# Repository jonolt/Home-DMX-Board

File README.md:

# Home DMX - Hardware

is a simple arduino based DMX controller to controll led lights installed in your home to be used with DMX controllers and relais.

**Please Contact me if you wonna use the board, there may be unducumented bugs.**

The Firmware can be found in a extra git repository: [Home-DMX-Firmaware](https://github.com/jonolt/Home-DMX-Firmaware).

This Project started with [Home-DMX-Control](https://github.com/jonolt/Home-DMX-Control). Firmware and hardware are now in two repositories.

## Idea

The selection for the lighting scene in daily use should be as simple as possible. Therefore exactly two push buttons are used to move up and down in a list of lighting scenes. Since I am not a fan of idle transformers, a conventional light switch is used in my application to switch the whole system on and off. In the same way a corresponding scene could be set.

The individual scenes should be adjustable directly on the controller without additional hardware. The input of the scenes works like on lighting control desks without motor faders via potentiometer and buttons. To make the firmware easy (without programmer and co) and maintainable by everyone, an Arduino was used, because it has a USB converter and the IDE is easy to use and install.

The board has a DMX output and 4 PWM/IO Outputs as well as 2 inputs for button.

## Structure

The MAX481 (U2) is a transceiver for RS-485 and RS-422 communication based on DMX. It uses the TX and RX pins of the arduino. For a visual control of the DMX communication Leds are connected via buffer (U61).

Digital inputs and outputs a isolated via optocouplers (additional circuits are required to switch larger loads).

The display is controlled serially (SPI) via the library provided by the manufacturer.

The switches can be hardware or software or both debaunced. Theres also the option to connect them via diodes (D1-D4) to a interupt pin.

The board does not has to be fully equipt with the componets.

**External Power must be disconnected when programming the Ardino, when a DC/DC converter is used!**

### Hardware Logic (Isolated)

#### Button Input

A total of 4 buttons can be placed on the pcb. While SW2 and SW3 are hard wired SW1 and SW4 can be set up in 4 different ways to safe pins to use the hardware interupt:

1. **1 buttons 0 extra IO**: SW1 or SW2 are connected only to the Interrupt pin via Diode D1/D4 or a bridge at D1/D4. If an innterupt is triggered, and neither SW2 or SW3 pin is pulled low, SW1 or SW4 must have been pressed.
2. **2 buttons 1 extra IO**: as in one but with JP1/JP2 bridged and SW1/SW4 fully equiped.
3. **2 buttons 2 extra IO**: equip all parts and bridge JP1 and JP2. Interrupt can still be used for other things.
4. **1 buttons 1 extra IO**: as in 3. but with either SW1 or SW4

Of course the swictehs can be used withiout the interrupt by ommiting the diodes. In fact even the low pass filete can be ommited with proper software debouncing.

All Switches and the interupt line are pulled up by R1 to R4 and R9. R4, C1 ect. build low pass filter for hardware debouncing and can be ommited (with the resistors bridged).

Swicth 2 and 3 have an additional Isolated input for external switches operating on another voltage level or with different ground.

#### LCD-Display

The LCD-Display is controlled by 3 Wire SPI connected to the Hardwre SPI of the microcontroller. The MISO master input is not required for the display and is kept free in case additional SPI devices are added (for example via a shield). The Backlight is PWM dimmed (D11) via the transisor Q1.

#### Expansion Connector J1 J2

The Connector(s) has the identical pinout as the Arduino Micro. Also you could use a stackable female connector strip directly with the Arduino.

#### LEDs

In addition to a power LED (D6), there are various Status LEDs on the front side (pcb-back) showing the correct function of the PWM Outputs (D20-23) and the DMX Interface (D60, D61). The LED of the Arduino can be used as a system LED if D13 is not used otherwise.

### Hardware Interfaces (Unisoltated)

All outputs and inputs (connectors) are isolated by default to each other. Resitor Bridges bridges can be apllied (1XX, 2XX) to break those isolations, see chapter Hardware Bridging.

#### X30 - Button Input

Simple current limiting Resistor R30 and R31 for diode of the photocoupler. Needs to be selected for each application by the input voltage V_IN with the formular:

R=(V_IN-V_F)/I_F, V_F=1.2V I_F=20mA

#### X40 - PWM/Output

These autputs can be used in 2 ways. As digital output with pullups and as Low Side switch (max 50mA, V_CE=0.1-0.2V).

The voltage for the pullups can cpme from the connector, directly bridged from the input power (R140) or via the linear voltage regulator U140, R142 and R143 (kater ones bridging isolation).

The emmiters of the photocouplers can be accessed directly via J41-J43 and J40-2. Conection between those can be broken at the Jumpers JP40-JP42. This way all four outputs can be used iolsated to each other.

#### X50 - Power In

Power input conssits of two parts revers voltage protection and DCDC-Converter. The reverse voltage protection is a siple p channel circuit. For the DCDC-Converter are two footprints obove each other. One for a SIL7 package (with pins 1,2,4,6 connected) and one for a SIL8 package (with pin (1, 2, (3), 6, 7 connected) to allow for different converters to be installed.

#### X60 - DMX

DMX uses the TX/RX pins of the arduino. The MAX481 (U60) is a common RS-485 tranciver. See [www.mathertel.de/Arduino/DMXShield.aspx](http://www.mathertel.de/Arduino/DMXShield.aspx) for a detailed description.

### Hardware Bridging

Danger Zone. Only assemble these components if you know what you are doing as this will bridge isolations.

#### 1XX

Bridges between unisolated interfaces:

- **R130, R131**: VIN/GND to PWM/Ouitput
- **R140, R141**: VIN/GND to Button Input

#### 2XX

Bridges between unisolated interfaces and isolated internal circuit:

- **J250, J251**: Connect these Pads with a wire to use the buildin voltage regulator of the arduino (VIN).
- **R260-R264**: Bypass isolation of DMX interface.

## License and Copyright

Copyright (C) 2019, 2020 Johannes Nolte
 
This program is free software: you can redistribute it and/or modify
it under the terms of the GNU General Public License as published by
the Free Software Foundation, version 2.1 only.

This program is distributed in the hope that it will be useful,
but WITHOUT ANY WARRANTY; without even the implied warranty of
MERCHANTABILITY or FITNESS FOR A PARTICULAR PURPOSE.  See the
GNU General Public License for more details.

You should have received a copy of the GNU General Public License
along with this program.  If not, see <https://www.gnu.org/licenses/>.

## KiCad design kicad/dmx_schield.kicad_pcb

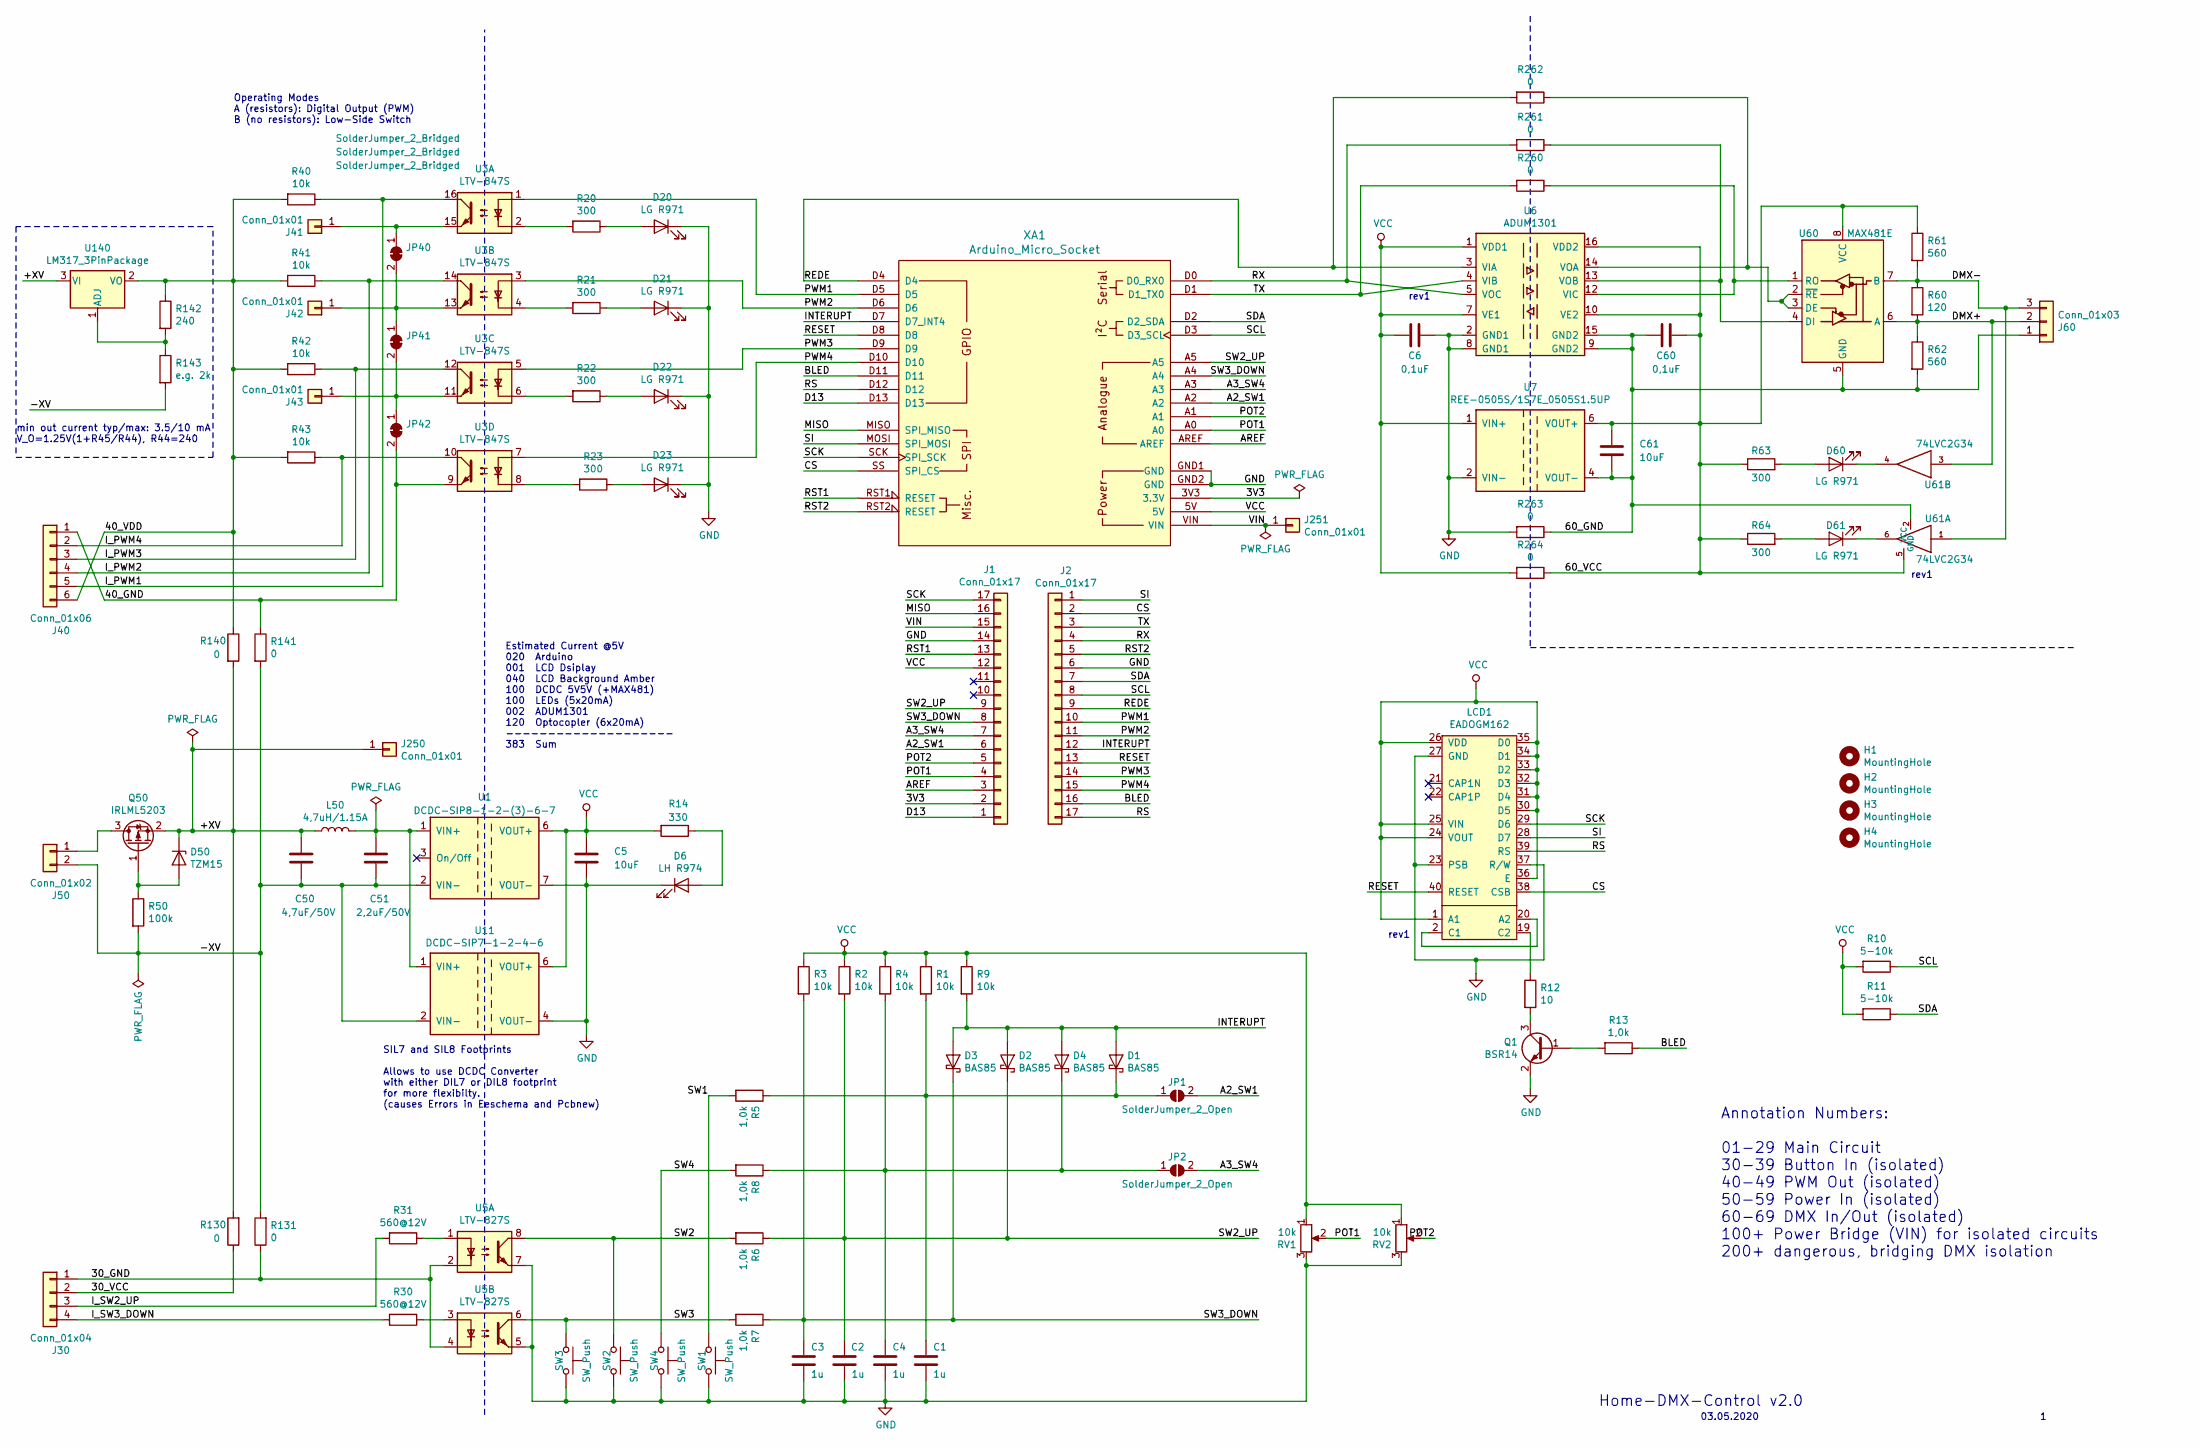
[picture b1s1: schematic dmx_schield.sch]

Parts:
C1, C2, C3, C4: 1u; C_0805_2012Metric
C5, C61: 10uF; C_1206_3216Metric
C6, C60: 0,1uF; C_0805_2012Metric
C50: 4,7uF/50V; C_1206_3216Metric
C51: 2,2uF/50V; C_1206_3216Metric
D1, D2, D3, D4: BAS85; D_MicroMELF
D6: LH R974; LED_0805_2012Metric
D20, D21, D22, D23, D60, D61: LG R971; LED_0805_2012Metric
D50: TZM15; D_SC-80
H1, H2, H3, H4: MountingHole; MountingHole_3.2mm_M3_DIN965
J1, J2: Conn_01x17; PinSocket_1x17_P2.54mm_Vertical
J30: Conn_01x04; PhoenixContact_MC_1,5_4-G-3.81_1x04_P3.81mm_Horizontal
J40: Conn_01x06; PhoenixContact_MC_1,5_6-G-3.81_1x06_P3.81mm_Horizontal
J41, J42, J43, J250, J251: Conn_01x01; SolderWirePad_1x01_Drill0.8mm
J50: Conn_01x02; PhoenixContact_MC_1,5_2-G-3.81_1x02_P3.81mm_Horizontal
J60: Conn_01x03; PhoenixContact_MC_1,5_3-G-3.81_1x03_P3.81mm_Horizontal
JP1, JP2: SolderJumper_2_Open; SolderJumper-2_P1.3mm_Open_Pad1.0x1.5mm
JP40, JP41, JP42: SolderJumper_2_Bridged; SolderJumper-2_P1.3mm_Bridged_Pad1.0x1.5mm
L50: 4,7uH/1.15A; L_Bourns-SRN4018
LCD1: EADOGM162; EA_DOGM_162
Q1: BSR14; SOT-23
Q50: IRLML5203; SOT-23
R1, R2, R3, R4, R9, R40, R41, R42, R43: 10k; R_0805_2012Metric
R5, R6, R7, R8, R13: 1,0k; R_0805_2012Metric
R10, R11: 5-10k; R_0805_2012Metric
R12: 10; R_0805_2012Metric
R14: 330; R_0805_2012Metric
R20, R21, R22, R23, R63, R64: 300; R_0805_2012Metric
R30, R31: 560@12V; R_0805_2012Metric
R50: 100k; R_0805_2012Metric
R60: 120; R_0805_2012Metric
R61, R62: 560; R_0805_2012Metric
R130, R131, R140, R141, R260, R261, R262, R263, R264: 0; R_0805_2012Metric
R142: 240; R_0805_2012Metric
R143: e.g. 2k; R_0805_2012Metric
RV1, RV2: 10k; Potentiometer_ACP_CA9-V10_Vertical
SW1, SW2, SW3, SW4: SW_Push; SW_SPST_PTS645
U1: DCDC-SIP8-1-2-(3)-6-7; SIP8-1-2-3-5-6-7-8
U3: LTV-847S; SMDIP-16_W7.62mm
U5: LTV-827S; SMDIP-8_W7.62mm
U6: ADUM1301; SOIC-16W_7.5x10.3mm_P1.27mm
U7: REE-0505S/1S7E_0505S1.5UP; SIP7-1-2-4-6
U11: DCDC-SIP7-1-2-4-6; SIP7-1-2-4-6
U60: MAX481E; PowerIntegrations_SO-8
U61: 74LVC2G34; SOT-23-6
U140: LM317_3PinPackage; SOT-223-3_TabPin2
XA1: Arduino_Micro_Socket

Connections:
/3V3: J1.2, XA1.3V3 (3.3V)
/30_GND: J30.1, R131.1, U5.2, U5.4
/30_VCC: J30.2, R130.1
/40_GND: J40.1, JP42.2 (B), R141.1, U3.9
/40_VDD: J40.6, R40.2, R41.2, R42.2, R43.2, R140.1, R142.1, U140.2 (VO)
/60_GND: C60.2, C61.1, J60.1, R62.2, R263.1, U6.9 (GND2), U6.15 (GND2), U7.4 (VOUT-), U60.5 (GND), U61.2 (GND)
/60_VCC: C60.1, C61.2, R61.1, R63.1, R64.1, R264.1, U6.10 (VE2), U6.16 (VDD2), U7.6 (VOUT+), U60.8 (VCC), U61.5 (VCC)
/+XV: C50.1, D50.1 (K), J250.1, L50.1, Q50.2 (S), R130.2, R140.2, U140.3 (VI)
/-XV: C50.2, C51.2, J50.2, R50.2, R131.2, R141.2, R143.2, U1.2 (VIN-), U11.2 (VIN-)
/A2_SW1: J1.6, JP1.2 (B), XA1.A2
/A3_SW4: J1.7, JP2.2 (B), XA1.A3
/AREF: J1.3, XA1.AREF
/BLED: J2.16, R13.1, XA1.D11
/CS: J2.2, LCD1.38 (CSB), XA1.SS (SPI_CS)
/D13: J1.1, XA1.D13
/DMX+: J60.2, R60.2, R62.1, U60.6 (A), U61.3
/DMX-: J60.3, R60.1, R61.2, U60.7 (B), U61.1
/INTERUPT: D1.2 (A), D2.2 (A), D3.2 (A), D4.2 (A), J2.12, R9.2, XA1.D7 (D7_INT4)
/I_PWM1: J40.5, R40.1, U3.16
/I_PWM2: J40.4, R41.1, U3.14
/I_PWM3: J40.3, R42.1, U3.12
/I_PWM4: J40.2, R43.1, U3.10
/I_SW2_UP: J30.3, R31.2
/I_SW3_DOWN: J30.4, R30.2
/MISO: J1.16, XA1.MISO (SPI_MISO)
/POT1: J1.4, RV1.2, XA1.A0
/POT2: J1.5, RV2.2, XA1.A1
/PWM1: J2.10, U3.1, XA1.D5
/PWM2: J2.11, U3.3, XA1.D6
/PWM3: J2.14, U3.5, XA1.D9
/PWM4: J2.15, U3.7, XA1.D10
/REDE: J2.9, R262.2, U6.3 (VIA), XA1.D4
/RESET: J2.13, LCD1.40 (RESET), XA1.D8
/RS: J2.17, LCD1.39 (RS), XA1.D12
/RST1: J1.13, XA1.RST1 (RESET)
/RST2: J2.5, XA1.RST2 (RESET)
/RX: J2.4, R261.2, U6.5 (VOC), XA1.D0 (D0_RX0)
/SCK: J1.17, LCD1.29 (D6), XA1.SCK (SPI_SCK)
/SCL: J2.8, R10.1, XA1.D3 (D3_SCL)
/SDA: J2.7, R11.1, XA1.D2 (D2_SDA)
/SI: J2.1, LCD1.28 (D7), XA1.MOSI (SPI_MOSI)
/SW1: R5.2, SW1.1
/SW2: R6.2, SW2.1, U5.8
/SW2_UP: C2.1, D2.1 (K), J1.9, R2.2, R6.1, XA1.A5
/SW3: R7.2, SW3.1, U5.6
/SW3_DOWN: C3.1, D3.1 (K), J1.8, R3.2, R7.1, XA1.A4
/SW4: R8.2, SW4.1
/TX: J2.3, R260.2, U6.4 (VIB), XA1.D1 (D1_TX0)
/VIN: J1.15, J251.1, XA1.VIN
GND: C1.2, C2.2, C3.2, C4.2, C5.1, C6.1, D6.1 (K), D20.1 (K), D21.1 (K), D22.1 (K), D23.1 (K), J1.14, J2.6, LCD1.23 (PSB), LCD1.27 (GND), LCD1.37 (R/W), Q1.2 (E), R263.2, RV1.3, RV2.3, SW1.2, SW2.2, SW3.2, SW4.2, U1.7 (VOUT-), U5.5, U5.7, U6.2 (GND1), U6.8 (GND1), U7.2 (VIN-), U11.4 (VOUT-), XA1.GND1 (GND), XA1.GND2 (GND)
unnamed: C1.1, D1.1 (K), JP1.1 (A), R1.2, R5.1
unnamed: C4.1, D4.1 (K), JP2.1 (A), R4.2, R8.1
unnamed: C51.1, L50.2, U1.1 (VIN+), U11.1 (VIN+)
unnamed: D6.2 (A), R14.1
unnamed: D20.2 (A), R20.1
unnamed: D21.2 (A), R21.1
unnamed: D22.2 (A), R22.1
unnamed: D23.2 (A), R23.1
unnamed: D50.2 (A), Q50.1 (G), R50.1
unnamed: D60.1 (K), U61.4
unnamed: D60.2 (A), R63.2
unnamed: D61.1 (K), U61.6
unnamed: D61.2 (A), R64.2
unnamed: J41.1, JP40.1 (A), U3.15
unnamed: J42.1, JP40.2 (B), JP41.1 (A), U3.13
unnamed: J43.1, JP41.2 (B), JP42.1 (A), U3.11
unnamed: J50.1, Q50.3 (D)
unnamed: LCD1.2 (C1), LCD1.20 (A2)
unnamed: LCD1.19 (C2), R12.1
unnamed: Q1.1 (B), R13.2
unnamed: Q1.3 (C), R12.2
unnamed: R20.2, U3.2
unnamed: R21.2, U3.4
unnamed: R22.2, U3.6
unnamed: R23.2, U3.8
unnamed: R30.1, U5.3
unnamed: R31.1, U5.1
unnamed: R142.2, R143.1, U140.1 (ADJ)
unnamed: R260.1, U6.12 (VIC), U60.1 (RO)
unnamed: R261.1, U6.13 (VOB), U60.4 (DI)
unnamed: R262.1, U6.14 (VOA), U60.2 (~RE), U60.3 (DE)
VCC: C5.2, C6.2, J1.12, LCD1.1 (A1), LCD1.24 (VOUT), LCD1.25 (VIN), LCD1.26 (VDD), LCD1.30 (D5), LCD1.31 (D4), LCD1.32 (D3), LCD1.33 (D2), LCD1.34 (D1), LCD1.35 (D0), LCD1.36 (E), R1.1, R2.1, R3.1, R4.1, R9.1, R10.2, R11.2, R14.2, R264.2, RV1.1, RV2.1, U1.6 (VOUT+), U6.1 (VDD1), U6.7 (VE1), U7.1 (VIN+), U11.6 (VOUT+), XA1.5V

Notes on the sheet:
03.05.2020
Operating Modes A (resistors): Digital Output (PWM) B (no resistors): Low-Side Switch
Estimated Current @5V 020 Arduino 001 LCD Dsiplay 040 LCD Background Amber 100 DCDC 5V5V (+MAX481) 100 LEDs (5x20mA) 002 ADUM1301 120 Optocopler (6x20mA) -------------------- 383 Sum
Annotation Numbers: 01-29 Main Circuit 30-39 Button In (isolated) 40-49 PWM Out (isolated) 50-59 Power In (isolated) 60-69 DMX In/Out (isolated) 100+ Power Bridge (VIN) for isolated circuits 200+ dangerous, bridging DMX isolation
SIL7 and SIL8 Footprints Allows to use DCDC Converter with either DIL7 or DIL8 footprint for more flexibilty. (causes Errors in Eeschema and Pcbnew)
min out current typ/max: 3.5/10 mA V_O=1.25V(1+R45/R44), R44=240
Home-DMX-Control v2.0
rev1

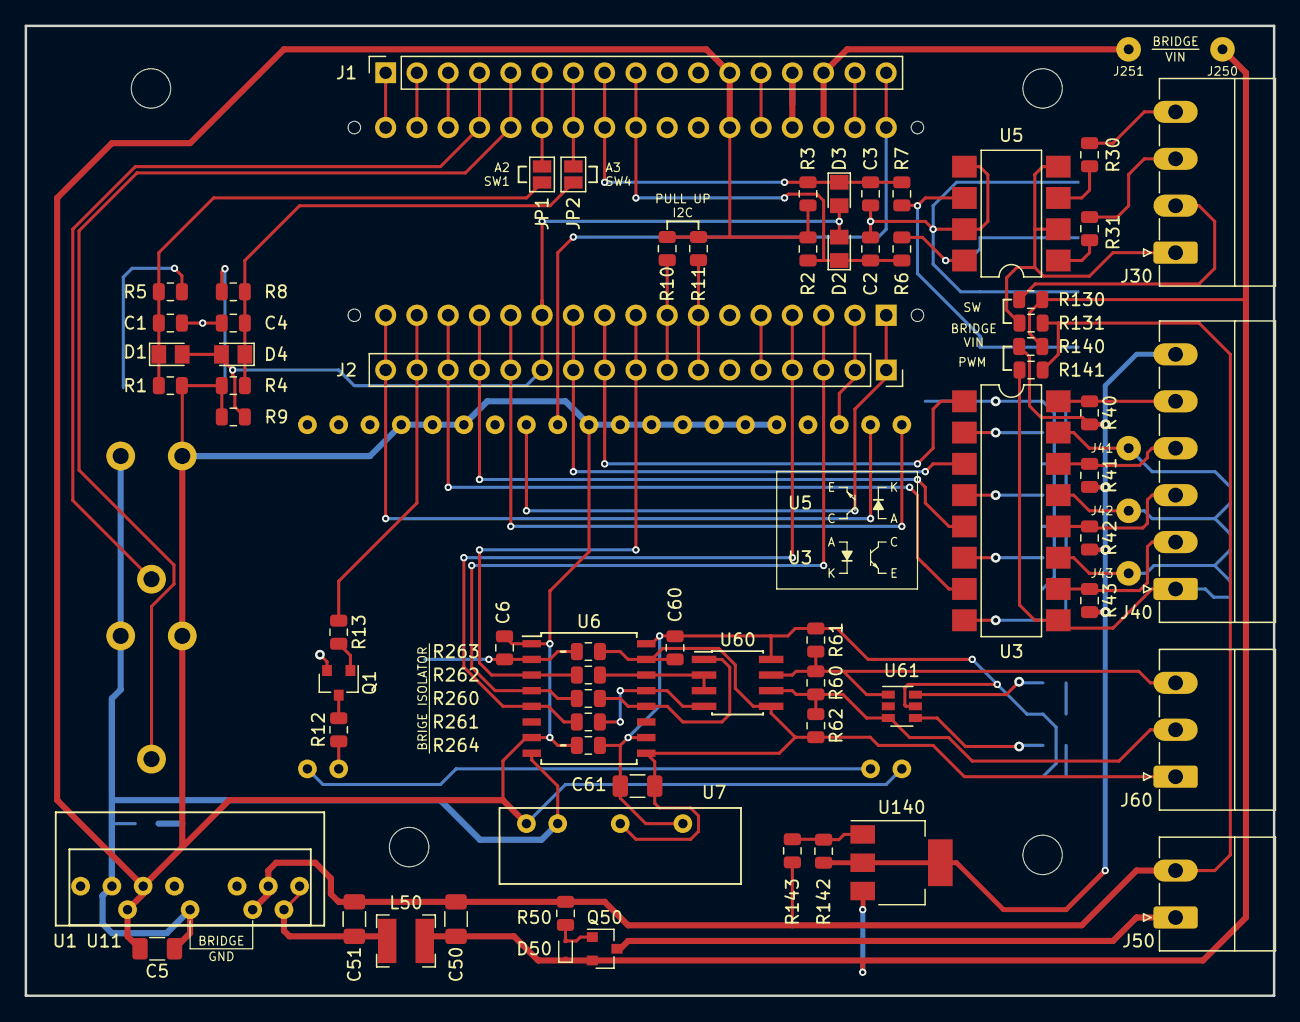
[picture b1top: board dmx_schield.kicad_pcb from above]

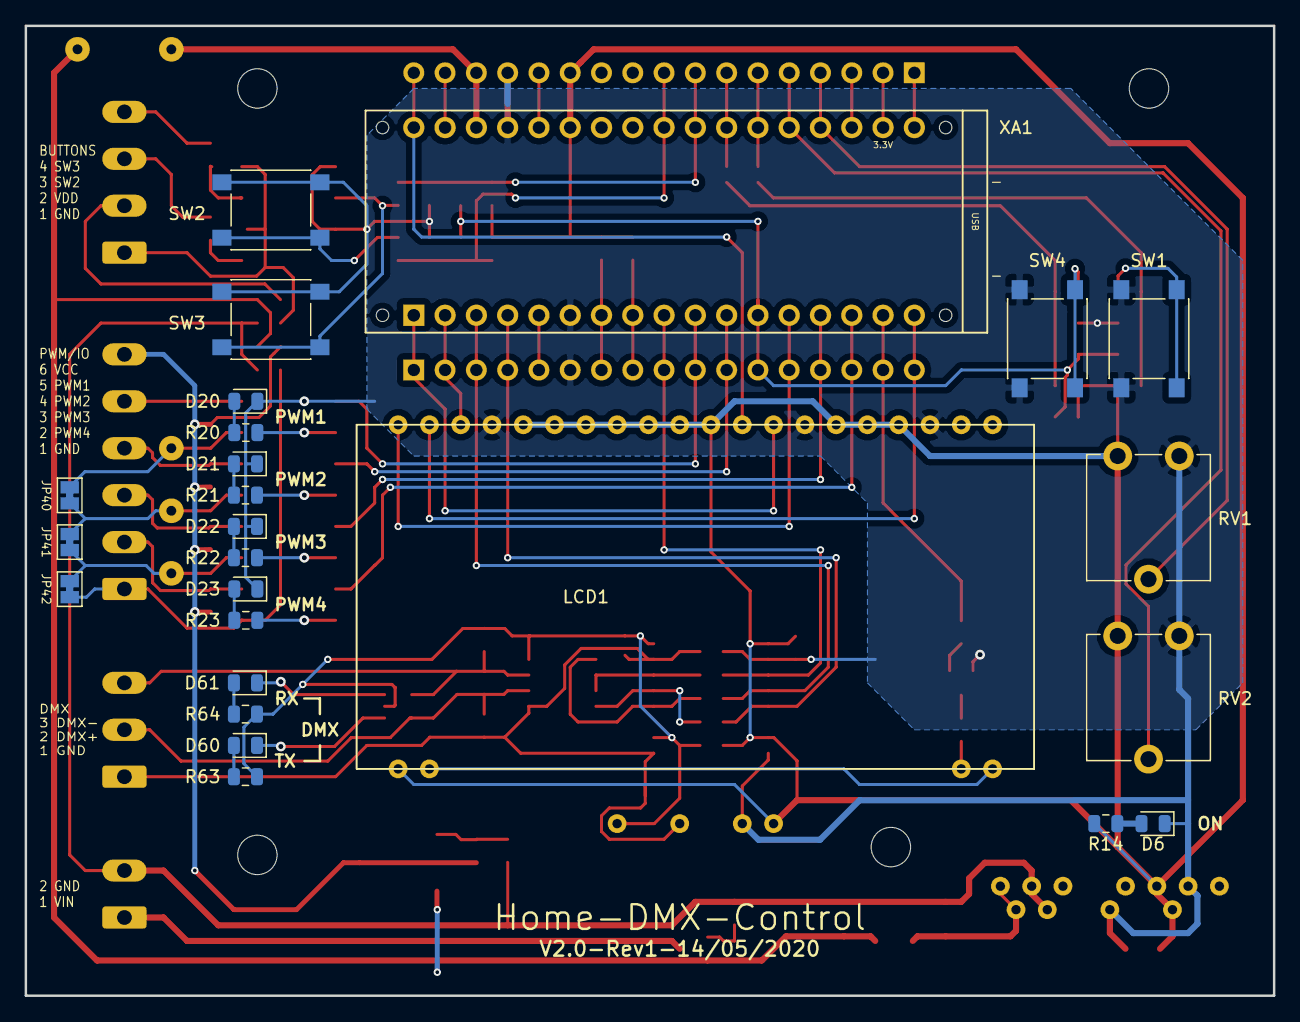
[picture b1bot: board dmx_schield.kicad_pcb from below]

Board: 2 copper layers, 101.3 x 78.7 mm, 103 parts (25 on the bottom side), 82 nets.

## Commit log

2020-05-07 added reference added to starting project
2020-05-19 fixed routing errors and error in library
    tested is everything, but the DMX circuit and LDO
